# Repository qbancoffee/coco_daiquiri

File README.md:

# CoCo Daiquiri
A drop in replacement board for the SC77526P DAC chip found in the Tandy CoCo's

- [View PDF version of the schematic](color_computer_dac.pdf)
- [How to order from JLCPCB](#Ordering-the-board)

This board replaces the functionality of the SC77526P DAC chip found in the Tandy CoCo's. 
The DAC chip is one of the custom linear integrated circuits used in the Color Computer
2 and 3. As its name implies, it contains a Digital to Analog Converter.
This chip also contains a sound multiplexer and the circuitry necessary to interface the joystick
controllers to the microprocessor.

I designed it using available parts from JLCPCB to reduce assembly time and to bring down the cost.

- [Download the latest release](https://github.com/qbancoffee/coco_daiquiri/releases/tag/1.1.0)<br>

## Goals
- [x] Generate sound.
- [x] Route sound.
- [x] Read Joysticks.
- [x] Input analog sound.
- [x] Output sound data to save to cassette.

All goals were met!!!<br>
- [Video testing the Daiquiri board with NitrOS9 and the Joey-HighRes](https://youtu.be/EgFfznWoyZE)
- [Video testing most of the functions of the Daiquiri](https://youtu.be/KFkKGCwIwdY)
- [Video saving a BASIC program using the Daiquiri board](https://youtu.be/1Up1ANTkjJg)
- [Video testing Rev 1 of the DAC replacement board AKA the Daiquiri ](https://youtu.be/-PZM2CGa1yw)

## Layout

## 3D rendering and pictures of it installed

<br>
<br>

<br>
CoCo 3 with Daiquiri chip installed

<br>

## Daiquiri and DAC

## Ordering the board
First Thing to do is clone this repository or download the latest release.
- [Download the latest release](https://github.com/qbancoffee/coco_daiquiri/releases/tag/1.1.0)<br>
All the files you'll need are in the gerber folder.

Many PCB manufacturers provide proprietary EDA software with nice and helpful features to help the user decrease the time and difficulty when designing a PCB. Unfortunately sometimes these programs will only allow you to order from that specific manufacturer. This is good for the manufacturer because it increases the odds that the person will order from them again because of the amount of time invested in learning to use that specific EDA program.

There are very nice EDA programs that will allow to design a PCB really quickly with fewer errors when it comes to components and footprints. Some of these programs are free to download and use for a trial period but after finishing your design sometimes you'll find that in order to export your design files so that you can actually order the boards you have to purchase a license. Sometimes you'll also find that there is a total area limit on the size of your design unless you buy a license. Companies use these tactics to make money and I really can't blame them because they have to make a living somehow.

I guess the question you might be asking is "Is there a specific PCB manufacturer I must use for a PCB designed with KiCAD?" The answer is no.
PCB manufacturers will still take your business even if you've elected to use another piece of software for your design so long as you can provide the Gerber files for your design. The Gerber format is an open ASCII vector format for printed circuit board (PCB) designs. It is the de facto standard used by PCB industry software to describe the printed circuit board images: copper layers, solder mask, legend, drill data, etc.

KiCAD has a bit of learning curve to it but once you are familiar with its quirks you'll find that having no limits on size, layers, components ect for your design is really nice and worth your investment in time. Also, being completely free, having no vendor association, and having no licensing issues  means that you can start using right it away without worries and when you're done just create the gerber files.

You can open the PCB design and create the gerber files yourself but I've already done that for the board so all you have to do is download the zip archive and upload it to your PCB manufacturer of choice. Click on the link below to download the gerber files.
<BR>
- [Download the gerber files](https://github.com/qbancoffee/coco_daiquiri/raw/main/gerber/daiquiri_gerber.zip)

There are a ton of PCB manufactures to choose from but recently I've been using [JLPCB](https://jlcpcb.com/) because the quality is good and they are well priced. JLPCB will even provide an automated online quote for pcb manufacturing and assembly. Once ordered they should arrive in the mail.
Obviously you can use any PCB manufacturer you wish.

Some manufacturers also have assembly services with costs varying based on the number of components, packaging and size of the board. 
Surface mount components are difficult to solder onto a board by hand but are perfect for automated PCB assembly making it much cheaper when it comes to using an assembly service. I chose to design these boards using surface mount components from LCSC's inventory so that JLCPCB can mostly assemble them.

To order the components you'll need a Bill Of Materials or a BOM. I've included a BOM for the board in the repo and just like the gerber files, they will be in the repo once you download it. Click on the link below to download the BOM.
<BR>
- [View BOM for the Daiquiri board](https://github.com/qbancoffee/coco_daiquiri/raw/main/color_computer_dac_1.1.0_BOM.csv)

The BOM includes LCSC part numbers so you can order them from JLCPCB, manufacturer part numbers so can search for the parts sold by other vendors, and other nice pieces of information to help you along.

To assemble the board JLCPCB will need to know the part locations and orientations, this information is in the CPL file.
- [View the CPL file](https://github.com/qbancoffee/coco_daiquiri/raw/main/color_computer_dac-all_1.1.0_POS.csv)  

- Go to jlcpcb and create an account if you don't have one.
- Click on "Quote Now" and then click on "Add Gerber File"
- Select "daiquiri_gerber.zip
- Scroll down and select "Free SMT Assembly for your PCB order"
- Select "Assemble Top side" and agree to the terms and conditions.
- Click on "Add BOM" and select "color_computer_dac_1.1.0_BOM.csv"
- Click on "Add CPL file" and select "color_computer_dac-all_1.1.0_POS.csv"
- Click "Next" and go over the components and pricing.
- Click "Next" or "Save to Cart".
  
  If you like the price, order it and you should receive a mostly assembled board.
  
Beacuse they are through hole components you'll have to solder the pin headers yourself. However, I just found out that JLCPCB offers hand soldering services now so you may want to look into that.....
  
  If you don't have 2.54 mm pitch breakaway pin headers laying around you can order from many places.
  - Amazon
  - Digikey
  - Mouser
  
  Here is a machine pin version which works better for the different type of sockets out there.<br>
  https://www.ebay.com/itm/155119535147<br>
  Thanks for the suggestion RETRO Innovations!

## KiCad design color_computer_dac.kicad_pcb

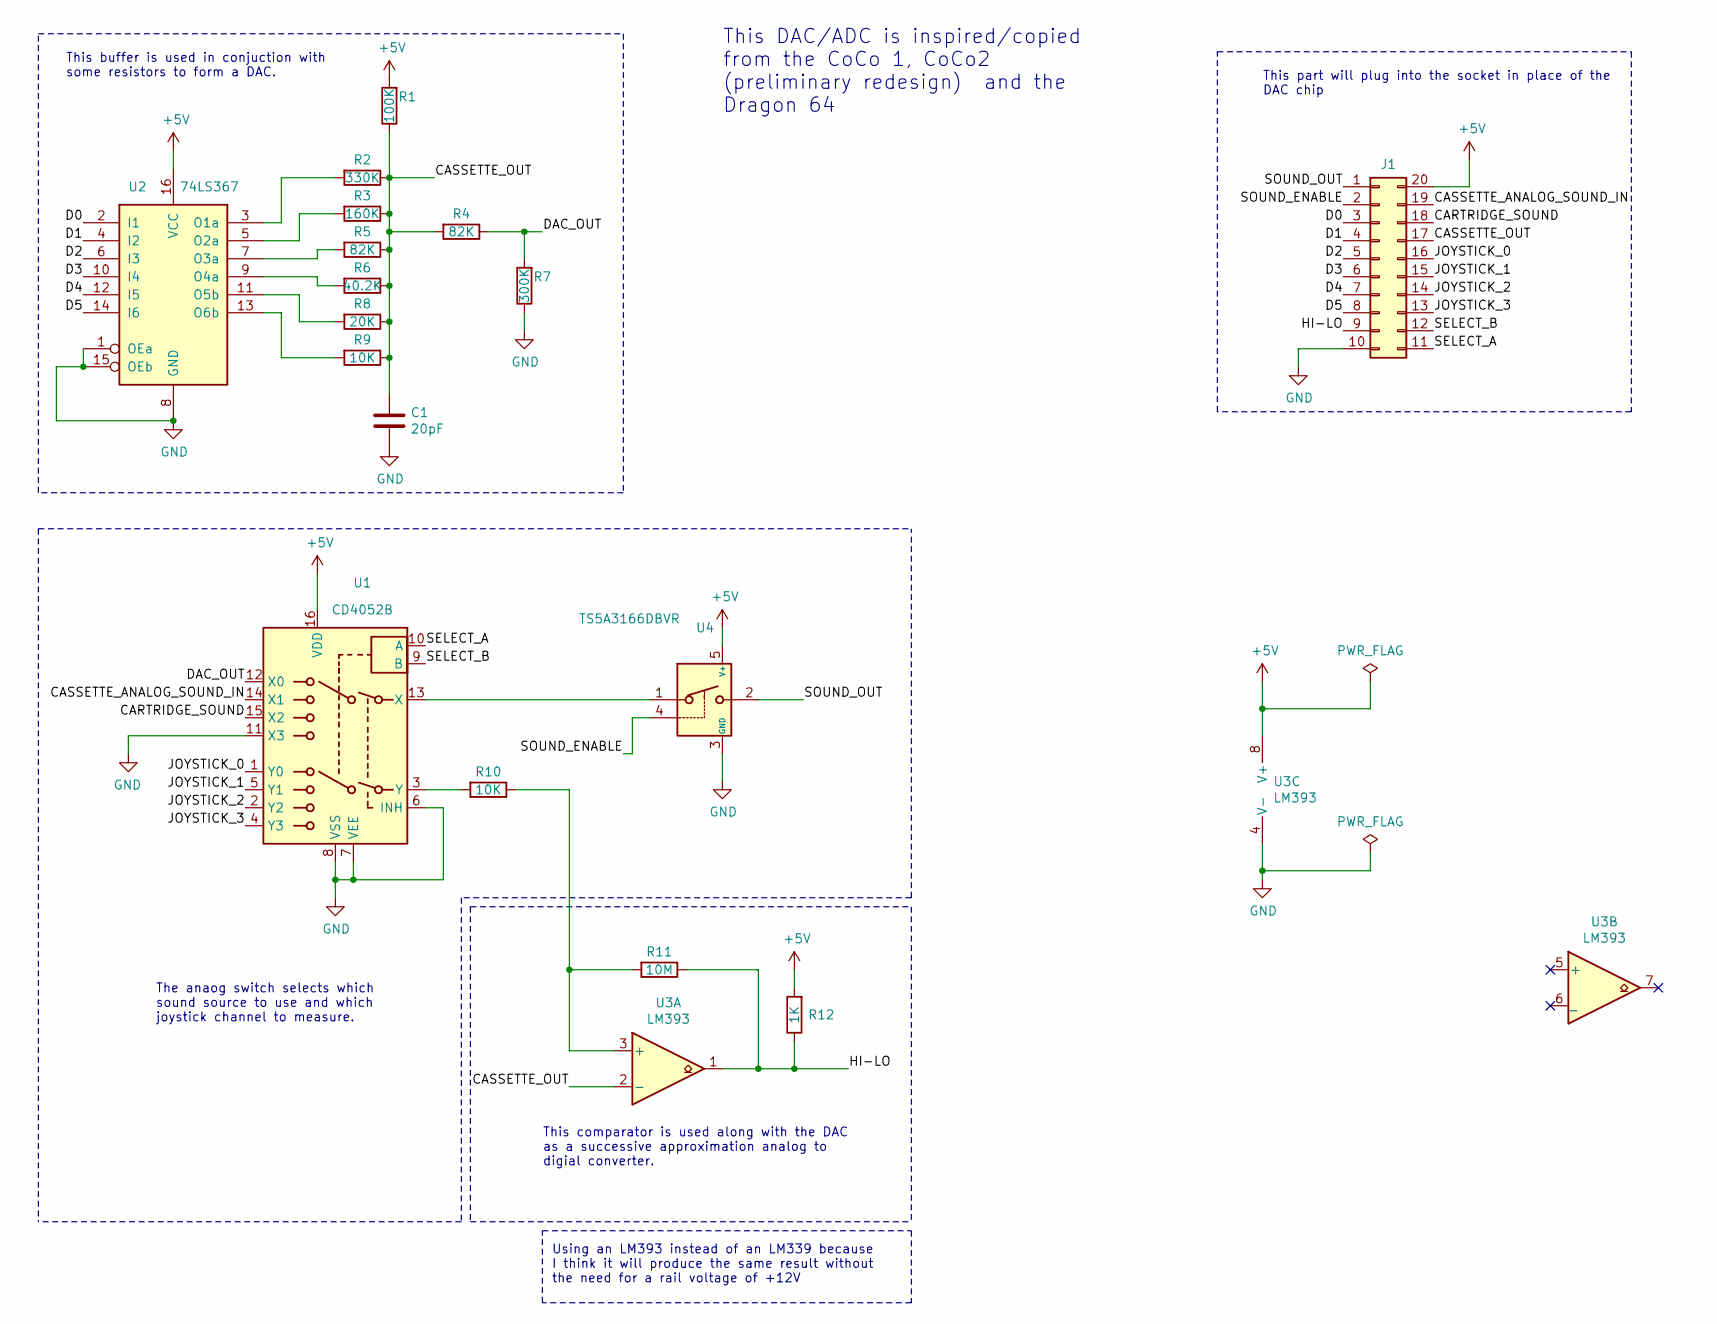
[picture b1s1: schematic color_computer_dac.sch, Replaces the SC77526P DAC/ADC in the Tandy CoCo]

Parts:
C1: 20pF; C_0805_2012Metric_Pad1.18x1.45mm_HandSolder; Manufacturer part# CL21C200JBANNNC
J1: Conn_02x10_Counter_Clockwise; DIP-20_W7.62mm_Socket
R1: 100K; R_0603_1608Metric_Pad0.98x0.95mm_HandSolder; Manufacturer part# 0603WAF1003T5E
R2: 330K; R_0805_2012Metric_Pad1.20x1.40mm_HandSolder; Manufacturer part# 0805W8F3303T5E
R3: 160K; R_0603_1608Metric_Pad0.98x0.95mm_HandSolder; Manufacturer part# 0603WAF1603T5E
R4, R5: 82K; R_0805_2012Metric_Pad1.20x1.40mm_HandSolder; Manufacturer part# 0805W8F8202T5E
R6: 40.2K; R_0603_1608Metric_Pad0.98x0.95mm_HandSolder; Manufacturer part# 0603WAF4022T5E
R7: 300K; R_0805_2012Metric_Pad1.20x1.40mm_HandSolder; Manufacturer part# 0805W8F3003T5E
R8: 20K; R_0805_2012Metric_Pad1.20x1.40mm_HandSolder; Manufacturer part# 0805W8F2002T5E
R9, R10: 10K; R_0805_2012Metric_Pad1.20x1.40mm_HandSolder; Manufacturer part# 0805W8F1002T5E
R11: 10M; R_0805_2012Metric_Pad1.20x1.40mm_HandSolder; Manufacturer part# 0805W8F1005T5E
R12: 1K; R_0805_2012Metric_Pad1.20x1.40mm_HandSolder
U1: CD4052B; HTSSOP-16-1EP_4.4x5mm_P0.65mm_EP3x3mm; Manufacturer part# MC74HC4052ADTR2G
U2: 74LS367; SOIC-16_3.9x9.9mm_P1.27mm; Manufacturer part# SN74LS367ADR
U3: LM393; TSSOP-8_4.4x3mm_P0.65mm; Manufacturer part# LM393PT
U4: TS5A3166DBVR; SOT-23-5; Manufacturer part# TS5A3166DBVR

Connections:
+5V: J1.20, R1.2, R12.2, U1.16 (VDD), U2.16 (VCC), U3.8 (V+), U4.5 (V+)
/CARTRIDGE_SOUND: J1.18, U1.15 (X2)
/CASSETTE_ANALOG_SOUND_IN: J1.19, U1.14 (X1)
/CASSETTE_OUT: C1.1, J1.17, R1.1, R2.1, R3.1, R4.2, R5.1, R6.1, R8.1, R9.1, U3.2 (-)
/D0: J1.3, U2.2 (I1)
/D1: J1.4, U2.4 (I2)
/D2: J1.5, U2.6 (I3)
/D3: J1.6, U2.10 (I4)
/D4: J1.7, U2.12 (I5)
/D5: J1.8, U2.14 (I6)
/DAC_OUT: R4.1, R7.2, U1.12 (X0)
/HI-LO: J1.9, R11.1, R12.1, U3.1
/JOYSTICK_0: J1.16, U1.1 (Y0)
/JOYSTICK_1: J1.15, U1.5 (Y1)
/JOYSTICK_2: J1.14, U1.2 (Y2)
/JOYSTICK_3: J1.13, U1.4 (Y3)
/SELECT_A: J1.11, U1.10 (A)
/SELECT_B: J1.12, U1.9 (B)
/SOUND_ENABLE: J1.2, U4.4
/SOUND_OUT: J1.1, U4.2
GND: C1.2, J1.10, R7.1, U1.6 (INH), U1.7 (VEE), U1.8 (VSS), U1.11 (X3), U2.1 (OEa), U2.8 (GND), U2.15 (OEb), U3.4 (V-), U4.3 (GND)
unnamed: R2.2, U2.3 (O1a)
unnamed: R3.2, U2.5 (O2a)
unnamed: R5.2, U2.7 (O3a)
unnamed: R6.2, U2.9 (O4a)
unnamed: R8.2, U2.11 (O5b)
unnamed: R9.2, U2.13 (O6b)
unnamed: R10.1, R11.2, U3.3 (+)
unnamed: R10.2, U1.3 (Y)
unnamed: U1.13 (X), U4.1

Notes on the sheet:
Using an LM393 instead of an LM339 because I think it will produce the same result without the need for a rail voltage of +12V
This DAC/ADC is inspired/copied from the CoCo 1, CoCo2 (preliminary redesign) and the Dragon 64
This comparator is used along with the DAC as a successive approximation analog to digial converter.
This part will plug into the socket in place of the DAC chip
This buffer is used in conjuction with some resistors to form a DAC.
The anaog switch selects which sound source to use and which joystick channel to measure.

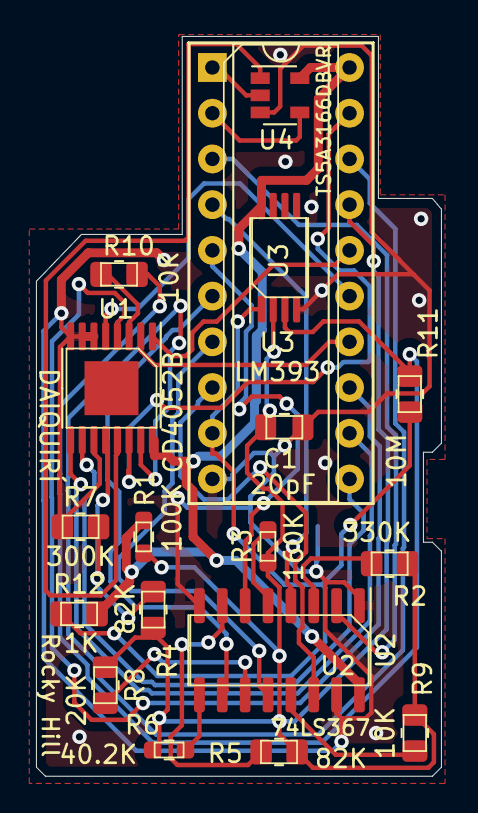
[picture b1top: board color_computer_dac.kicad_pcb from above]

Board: 2 copper layers, 22.5 x 41.1 mm, 18 parts (0 on the bottom side), 30 nets.

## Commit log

2021-11-19 modified readme
2021-11-19 modified README.txt
